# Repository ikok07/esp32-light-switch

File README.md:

# ESP32 Light Switch

A BLE-enabled smart light switch built on the **ESP32**, developed as part of a custom hardware product lineup. The firmware is written in C using the **ESP-IDF** framework and integrates natively with **Home Assistant** via a custom dedicated [HAOS BLE integration](https://github.com/ikok07/kok-products-ble-haos-integration).

---

## Features

- **BLE Control** — Toggle the light on/off wirelessly from any BLE-capable client (preferably the HAOS integration)
- **Physical Toggle** — Interrupt-driven physical button for manual control (GPIO 21)
- **Home Assistant Integration** — Works out of the box with my custom [HAOS BLE integration](https://github.com/ikok07/kok-products-ble-haos-integration)
- **Status LED** — RGB LED (GPIO 48) that reflects the current device state at a glance
- **Light Sleep** — CPU frequency scaling and light sleep enabled at runtime to reduce power consumption
- **Dual-core task scheduling** — BLE stack runs on Core 0; light control, status LED, and notification tasks run on Core 1

---

## Hardware

The PCB design files are located in the [`pcb/`](pcb/) directory (KiCad project). Key datasheets and reference material can be found in [`docs/`](docs/).

| Component         | Purpose             |
|-------------------|---------------------|
| ESP32             | Main MCU            |
| BTB16 - TRIAC     | Mains switching     |
| HLK-PM01          | AC→5 V power supply |
| MIC5205 LDO       | 3.3 V regulation    |
| PC817 Optocoupler | TRIAC isolation     |

---

## Firmware Overview

The project is structured as a standard ESP-IDF project with reusable components:

```
main/           – Application entry point & board-specific configuration
components/
  ├── app_state/        – Global application state (tasks, handles, shared values)
  ├── ble/              – BLE driver (GAP / GATT abstraction over NimBLE)
  ├── logger/           – Logging utilities
  ├── power/            – CPU frequency control & light sleep management
  ├── shared_values/    – Thread-safe shared value store (FreeRTOS-based)
  ├── tasks_scheduler/  – FreeRTOS task lifecycle helpers
  └── timer/            – Timer utilities
```

### Startup sequence

1. Application state initialised
2. Logger configured
3. Power management configured & CPU frequency scaling enabled
4. Status LED initialised → **orange** (configuring)
5. Light control GPIO and ISR configured
6. BLE stack initialised → status LED turns **white** (ready to connect)
7. Light sleep enabled

### Status LED states

| Color     | State |
|-----------|-------|
| 🟠 Orange | Configuring / booting |
| 🔴 Red    | Hardware configuration error |
| 🔵 White  | Ready to connect |
| 🟢 Green  | Connected |
| Other     | BLE configuration error |

---

## BLE Profile

| Property             | Value                                           |
|----------------------|-------------------------------------------------|
| Device name          | `LSwitch`                                       |
| GAP appearance       | `0x04C1` (Generic Switch)                       |
| Advertising interval | 50 ms                                           |
| Security mode        | Disabled / Just Works                           |
| Max connections      | Configured via CONFIG_BT_NIMBLE_MAX_CONNECTIONS |
| Serial number        | `LS001`                                         |

### GATT Services

| Service        | UUID                                             | Description                                                  |
|----------------|--------------------------------------------------|--------------------------------------------------------------|
| Identifier     | `651535-36ae-49aa-354c-ecfec15bc888` (128-bit)   | Used by the HAOS integration to identify the device family   |
| Automation I/O | `0x1815`                                         | Exposes the light state characteristic                       |

**Light State Characteristic** (`0x2A56` – Digital):
- **Read** — returns current relay state (`0` or `1`)
- **Write** — sets relay state (`0` = off, `1` = on)
- **Notify** — pushes state updates to subscribed clients

---

## Home Assistant Integration

Install the [HAOS BLE integration](https://github.com/ikok07/kok-products-ble-haos-integration) in your Home Assistant instance. The device advertises the identifier service UUID and manufacturer data in its BLE advertisement so that the integration can automatically recognise and add it.

See [`docs/haos_compatibility.md`](docs/haos_compatibility.md) for the full BLE advertisement requirements.

---

## Building & Flashing

Prerequisites: [ESP-IDF v5.x](https://docs.espressif.com/projects/esp-idf/en/latest/esp32s3/get-started/) installed and sourced.

```bash
# Configure
idf.py set-target esp32

# Build
idf.py build

# Flash & monitor
idf.py -p /dev/tty.usbserial-* flash monitor
```

---

## License

This project is part of a custom hardware product lineup. All rights reserved © Kaloyan Stefanov.

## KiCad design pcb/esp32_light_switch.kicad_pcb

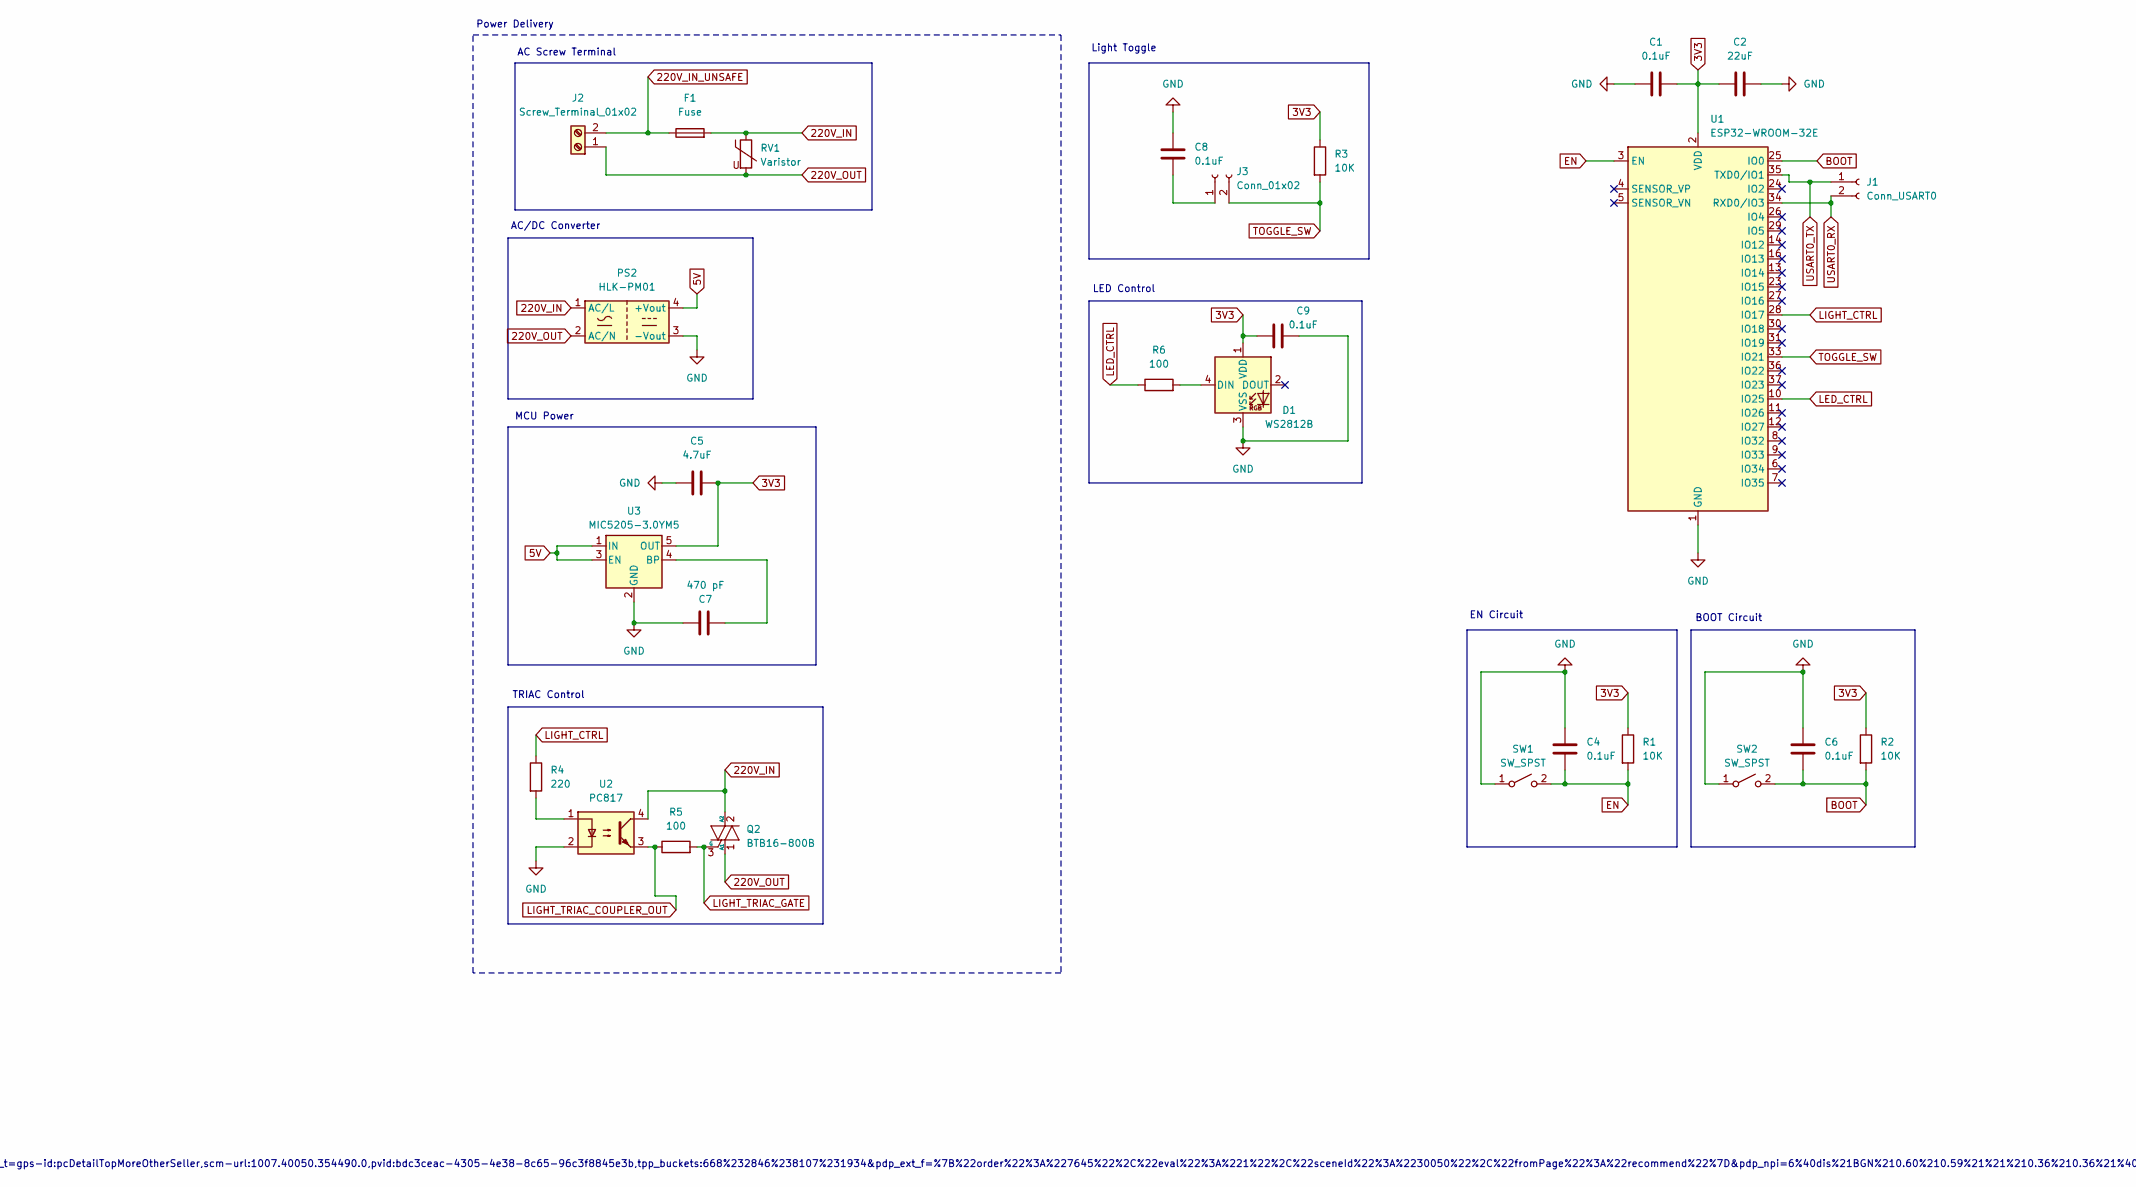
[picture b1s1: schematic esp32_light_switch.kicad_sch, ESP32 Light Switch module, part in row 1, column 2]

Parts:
C1, C4, C6, C8, C9: 0.1uF; C_0805_2012Metric_Pad1.18x1.45mm_HandSolder
C2: 22uF; C_0805_2012Metric_Pad1.18x1.45mm_HandSolder
C5: 4.7uF; CP_EIA-6032-20_AVX-F_HandSolder
C7: 470 pF; C_Disc_D5.0mm_W2.5mm_P5.00mm
D1: WS2812B; LED_WS2812B_PLCC4_5.0x5.0mm_P3.2mm
F1: Fuse; Fuseholder_Cylinder-5x20mm_Schurter_0031_8201_Horizontal_Op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
J1: Conn_USART0; PinHeader_1x02_P2.54mm_Vertical
J2: Screw_Terminal_01x02; DG3065002P1200AH
J3: Conn_01x02; PinHeader_1x02_P2.54mm_Vertical
PS2: HLK-PM01; Converter_ACDC_Hi-Link_HLK-PMxx
Q2: BTB16-800B; TO-220-3_Vertical
R1, R2, R3: 10K; R_0805_2012Metric_Pad1.20x1.40mm_HandSolder
R4: 220; R_0805_2012Metric_Pad1.20x1.40mm_HandSolder
R5, R6: 100; R_0805_2012Metric_Pad1.20x1.40mm_HandSolder
RV1: Varistor; RV_Disc_D12mm_W3.9mm_P7.5mm
SW1, SW2: SW_SPST; SW_TH_Tactile_Omron_B3F-100x
U1: ESP32-WROOM-32E; ESP32-WROOM-32D
U2: PC817; DIP-4_W7.62mm_SMDSocket_SmallPads
U3: MIC5205-3.0YM5; SOT-23-5

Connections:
3V3: C1.2, C2.1, C5.2, C9.1, D1.1 (VDD), R1.1, R2.1, R3.1, U1.2 (VDD), U3.5 (OUT)
5V: PS2.4 (+Vout), U3.1 (IN), U3.3 (EN)
220V_IN: F1.2, PS2.1 (AC/L), Q2.2 (A2), RV1.1, U2.4
220V_IN_UNSAFE: F1.1, J2.2
220V_OUT: J2.1, PS2.2 (AC/N), Q2.1 (A1), RV1.2
BOOT: C6.1, R2.2, SW2.2 (B), U1.25 (IO0)
EN: C4.2, R1.2, SW1.2 (B), U1.3 (EN)
GND: C1.1, C2.2, C4.1, C5.1, C6.2, C7.2, C8.1, C9.2, D1.3 (VSS), PS2.3 (-Vout), SW1.1 (A), SW2.1 (A), U1.1 (GND), U1.15 (GND), U1.38 (GND), U1.39 (GND), U2.2, U3.2 (GND)
LED_CTRL: R6.1, U1.10 (IO25)
LIGHT_CTRL: R4.1, U1.28 (IO17)
LIGHT_TRIAC_COUPLER_OUT: R5.1, U2.3
LIGHT_TRIAC_GATE: Q2.3 (G), R5.2
unnamed: D1.4 (DIN), R6.2
unnamed: C8.2, J3.1
unnamed: R4.2, U2.1
unnamed: C7.1, U3.4 (BP)
TOGGLE_SW: J3.2, R3.2, U1.33 (IO21)
USART0_RX: J1.2, U1.34 (RXD0/IO3)
USART0_TX: J1.1, U1.35 (TXD0/IO1)

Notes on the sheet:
TRIAC Control
Light Toggle
AC Screw Terminal
Power Delivery
LED Control
AC/DC Converter
BOOT Circuit
https://www.aliexpress.com/item/32901160058.html?spm=a2g0o.detail.pcDetailTopMoreOtherSeller.2.2347F34bF34bvB&gps-id=pcDetailTopMoreOtherSeller&scm=1007.40050.354490.0&scm_id=1007.40050.354490.0&scm-url=1007.40050.354490.0&pvid=bdc3ceac-4305-4e38-8c65-96c3f8845e3b&_t=gps-id:pcDetailTopMoreOtherSell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
MCU Power
EN Circuit

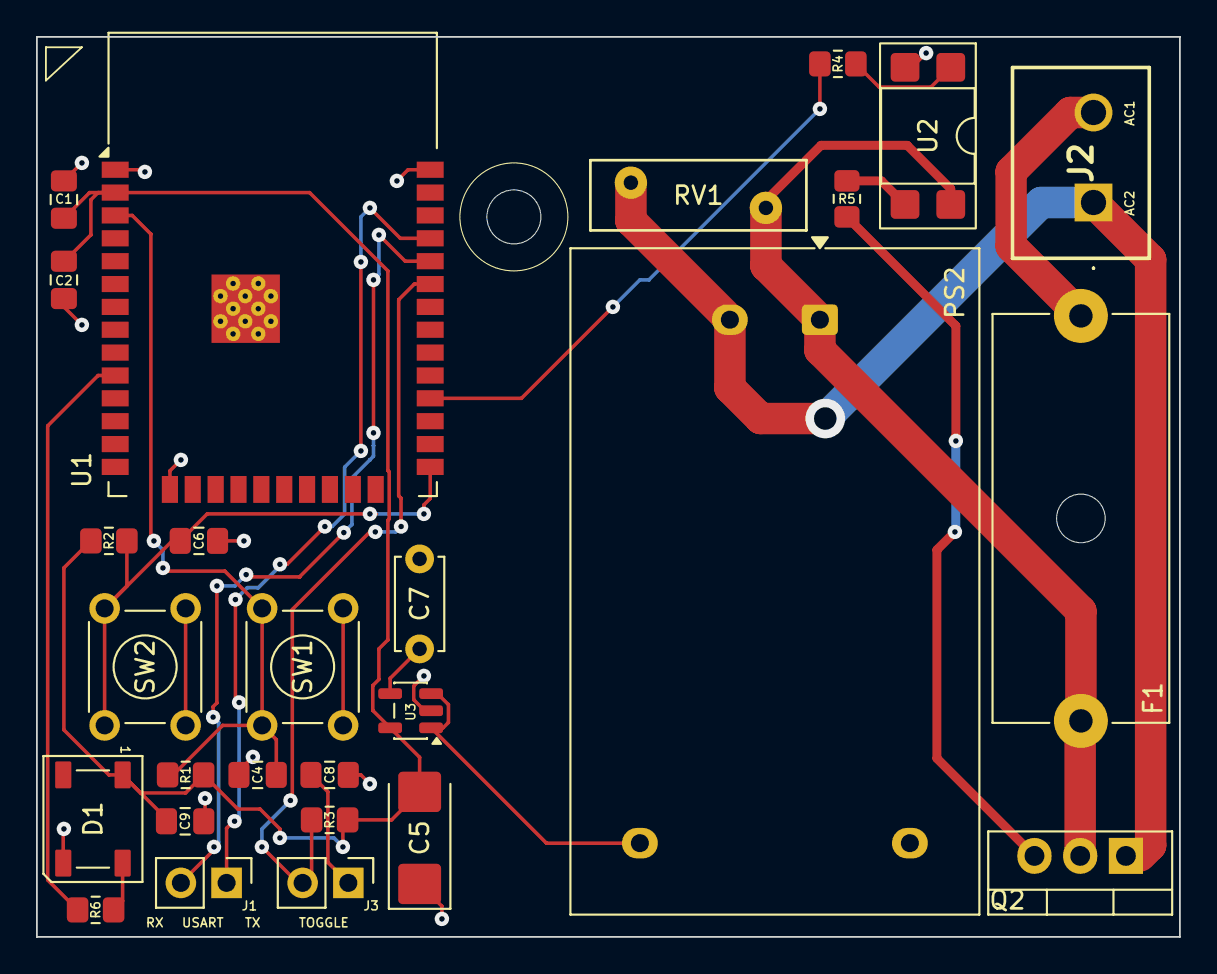
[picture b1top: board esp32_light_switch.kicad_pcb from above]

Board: 2 copper layers, 63.5 x 50.0 mm, 27 parts (0 on the bottom side), 19 nets.

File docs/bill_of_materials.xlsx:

Part | Designator | Quantity | Price | Real Price | URL
ESP32-WROOM-32E | U1 | 1 | 0 | 0
HLK-PM01 (Power supply) | PS2 | 1 | 4.3499999999999996 | 4.3499999999999996 | https://bulcomp-eng.com/m/index.php?p=10&idprod=19925
PC817 (Optocoupler) | U2 | 1 | 0.26 | 0.26 | https://tpetrov.com/ltv817s-lit-247331
BTB16-800BRG (TRIAC) | Q2 | 1 | 1.07 | 1.07 | https://tpetrov.com/btb16-800brg-242340
AC Terminal Screw 01x02 | J2 | 1 | 0.26 | 0.26 | https://tpetrov.com/klema-dg306-02p-36674
MIC5205 (Voltage regulator) | U3 | 1 | 0 | 0
Capacitor Tantalum (4.7uF) | C5 | 1 | 0.64 | 0.64 | https://tpetrov.com/kondenzator-47mf-25v-smd-tantal-35838
Capacitor (0.1uF) | C1, C4, C6, C8, C9 | 5 | 0.06 | 0.3 | https://tpetrov.com/kondenzator-100nf-50v-0805-smd-34785
Capacitor (470pF) | C7 | 1 | 0.08 | 0.08 | https://tpetrov.com/kondenzator-470pf-100v-47046
Capacitor (22uF) | C2 | 1 | 0.1 | 0.1 | https://tpetrov.com/kondenzator-22mf-63v-smd-0805-243684
Resistor (220) | R4 | 1 | 0.08 | 0.08 | https://tpetrov.com/rezistor-220om-smd-0805-250613
Resistor (10K) | R1, R2, R3 | 3 | 0.03 | 0.09 | https://tpetrov.com/rezistor-10kom-smd-0805-22597
Resistor (100) | R5, R6 | 2 | 0.06 | 0.12 | https://tpetrov.com/rezistor-100om-0125w-smd-22589
Touch button | SW1, SW2 | 2 | 0.09 | 0.18 | https://tpetrov.com/tach-buton-121-9505
Toggle button | J3 | 1 | 0.97 | 0.97 | https://tpetrov.com/buton-swb1019a-r-240936
Varistor 275V | RV1 | 1 | 0.36 | 0.36 | https://tpetrov.com/varistor-275v-125mm-240814
Fuse (500mA) | F1 | 1 | 0.1 | 0.1 | https://tpetrov.com/predpazitel-5x20-05a-zkm-36366
Fuse holder | - | 1 | 0.26 | 0.26 | https://tpetrov.com/darjach-za-predpazitel-f313-5x20-39121
Connector (Male & Female) | - | 1 | 0.1 | 0.1 | https://tpetrov.com/kuplung-396-ns39-02mg-46470
Heatsink (TRIAC) | - | 1 | 0.51 | 0.51 | https://tpetrov.com/radiator-n23-40566
WS2812B LED | D1 | 1 | 0 | 0 | -
 |  |  |  | 9.8299999999999965

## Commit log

2026-02-17 refactor code and advertise services
2026-02-21 improve application
2026-02-21 modify ble board specific dependencies
2026-02-22 remove .idea folder
2026-03-09 Implement light control task
2026-03-10 Refactor light control and add status LED functionality
2026-03-11 Refactor BLE configuration and light control initialization
2026-03-13 Add BLE light state notification task and update related configurations
2026-03-14 Refactor code to adapt to module changes
2026-03-26 Enhance BLE compatibility with Home Assistant integration by updating advertisement parameters and security settings
2026-03-28 Add KiCad PCB design files and update README for ESP32 light switch project
2026-03-28 Add PCB 3d model
2026-03-28 Fix README image url
2026-03-28 improve README
2026-03-28 refactor: Rename BLE configuration files and update CMake version
